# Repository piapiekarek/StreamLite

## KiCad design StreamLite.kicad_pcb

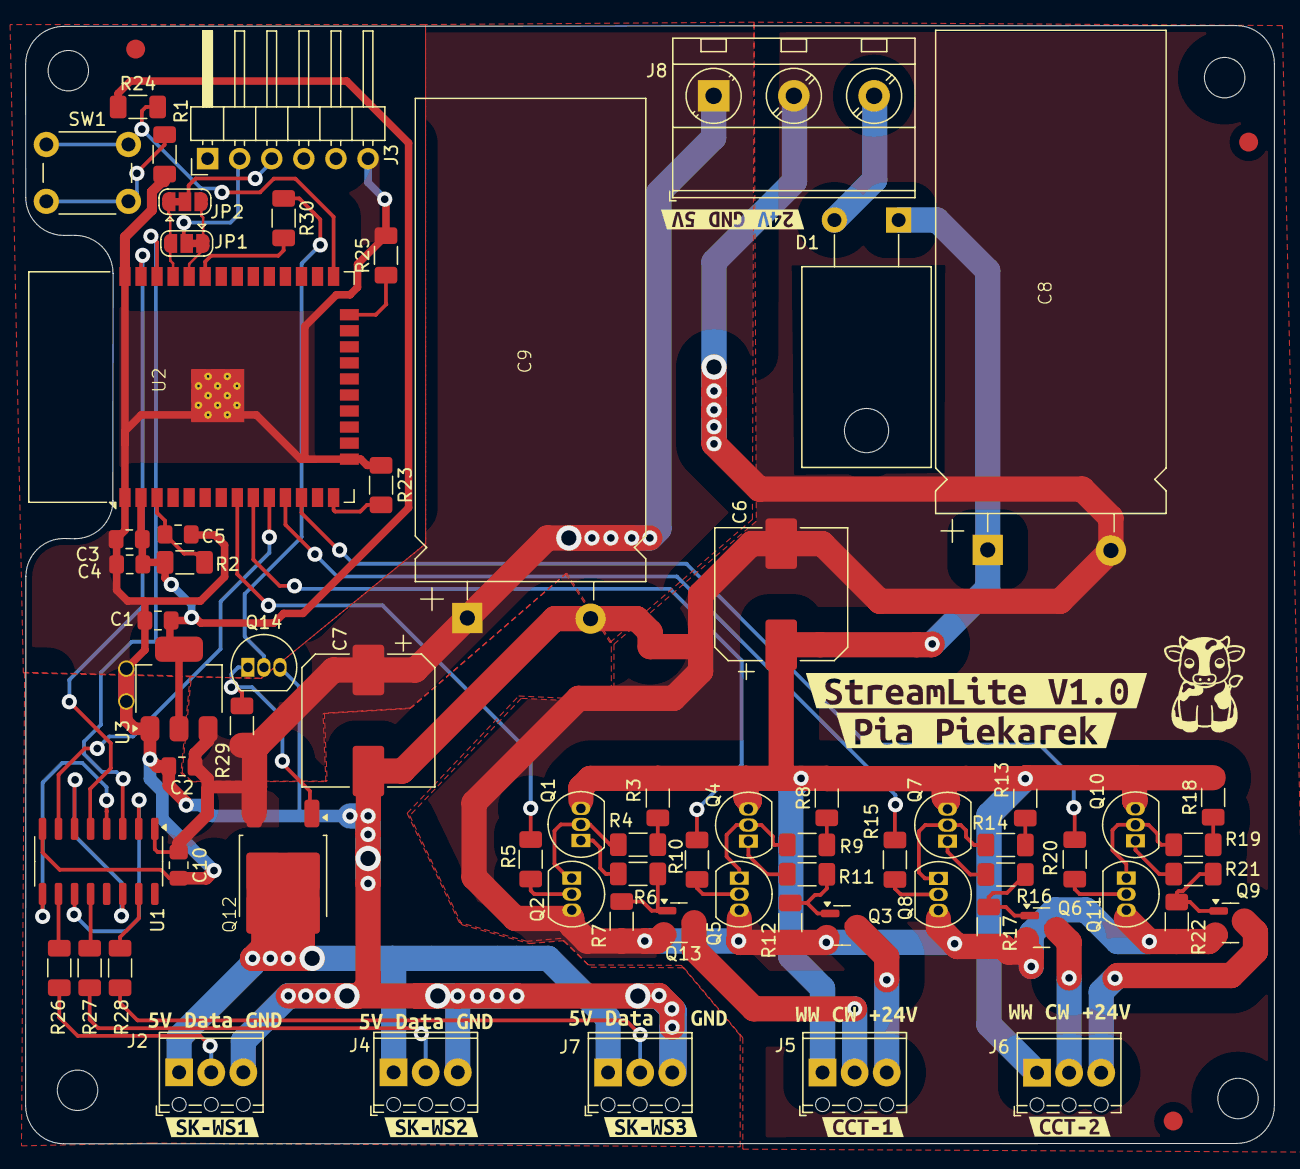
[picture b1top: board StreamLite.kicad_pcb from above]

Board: 2 copper layers, 98.8 x 88.5 mm, 90 parts (1 on the bottom side), 60 nets.

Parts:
C1, C3, C10: 100n; C_0805_2012Metric_Pad1.18x1.45mm_HandSolder
C2: 330n; C_0805_2012Metric_Pad1.18x1.45mm_HandSolder
C4: 10u; C_0805_2012Metric_Pad1.18x1.45mm_HandSolder
C5: 1u; C_0805_2012Metric_Pad1.18x1.45mm_HandSolder
C6, C7: 470u; CP_Elec_10x10
C8, C9: 10.000uF; Capacitor_L38.0mm_D18.0mm_P10_Horizontal
D1: D; TO-220-2_Horizontal_TabDown
FID1, FID2, FID3: Fiducial; Fiducial_1.5mm_Mask3mm
H1, H2, H3, H4: MountingHole; MountingHole_3.2mm_M3
J2, J4, J5, J6, J7: Screw_Terminal_01x03; TerminalBlock_Phoenix_MPT-0,5-3-2.54_1x03_P2.54mm_Horizontal
J3: Conn_01x06_Socket; PinHeader_1x06_P2.54mm_Horizontal
J8: Screw_Terminal_01x03; TerminalBlock_MetzConnect_Type701_RT11L03HGLU_1x03_P6.35mm_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
JP1, JP2: SolderJumper_3_Bridged12; SolderJumper-3_P1.3mm_Bridged12_RoundedPad1.0x1.5mm
NT1: NetTie_2; NetTie-2_SMD_Pad2.0mm
NT2: NetTie_2; NetTie-2_THT_Pad1.0mm
Q1, Q4, Q7, Q10: BC327; TO-92_Inline
Q2, Q5, Q8, Q11: BC337; TO-92_Inline
Q3, Q6, Q9, Q13: AO3400A; SOT-23
Q12: D4185; TO-252-3_TabPin2_D4185
Q14: BC547; TO-92_Inline
R1: 4k7; C_1206_3216Metric_Pad1.33x1.80mm_HandSolder
R2, R3, R5, R8, R10, R13, R15, R18, R20, R24: 10k; C_1206_3216Metric_Pad1.33x1.80mm_HandSolder
R4, R9, R14, R19: 22k; C_1206_3216Metric_Pad1.33x1.80mm_HandSolder
R6, R7, R11, R12, R16, R17, R21, R22, R26, R27, R28, R30: 1k; C_1206_3216Metric_Pad1.33x1.80mm_HandSolder
R23: 10k/DNP; C_1206_3216Metric_Pad1.33x1.80mm_HandSolder
R25: DNP; C_1206_3216Metric_Pad1.33x1.80mm_HandSolder
R29: 2k2; C_1206_3216Metric_Pad1.33x1.80mm_HandSolder
SW1: Boot; SW_PUSH_6mm_H5mm
U1: 4049; SO-16_3.9x9.9mm_P1.27mm
U2: ESP32-WROOM-32; ESP32-Wroom-32
U3: AMS1117-3.3; SOT-223-3_TabPin2
kibuzzard-670D97D1: G***; kibuzzard-670D97D1
kibuzzard-670D99B4, kibuzzard-670D99B4#2: G***; kibuzzard-670D99B4
kibuzzard-670D983B: G***; kibuzzard-670D983B
kibuzzard-670D998F: G***; kibuzzard-670D998F
kibuzzard-670D9849: G***; kibuzzard-670D9849
kibuzzard-670D9857: G***; kibuzzard-670D9857
kibuzzard-670EF237: G***; kibuzzard-670EF237
kibuzzard-670EF243: G***; kibuzzard-670EF243
kibuzzard-67243A6C: G***; kibuzzard-67243A6C
kibuzzard-67243A60: G***; kibuzzard-67243A60
kibuzzard-672436BF: G***; kibuzzard-672436BF
kibuzzard-67243969: G***; kibuzzard-67243969

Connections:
+3V3: C1.1, C3.1, C4.1, R2.1, R24.1, U2.2 (VDD), U3.2 (VO)
+5V: C2.1, C7.1, C9.1, C10.1, J8.1, Q12.3 (S), R29.2, U1.1 (VCC), U3.3 (VI)
+5VP: J2.1, J4.1, J7.1, Q12.1 (D)
+24V: C6.1, C8.1, D1.1 (K), J5.1, J6.1, Q1.3 (E), Q4.3 (E), Q7.3 (E), Q10.3 (E), R3.2, R8.2, R13.2, R18.2
/CW1: J5.2, Q13.3 (D)
/CW2: J6.2, Q6.3 (D)
/V_IN: D1.2 (A), J8.3
/WW1: J5.3, Q3.3 (D)
/WW2: J6.3, Q9.3 (D)
CCT1_CW: R15.1, U2.11 (IO26)
CCT1_WW: R20.1, U2.12 (IO27)
CCT2_CW: R5.1, U2.8 (IO32)
CCT2_WW: R10.1, U2.9 (IO33)
GND1: C6.2, C8.2, J8.2, NT1.1, Q2.3 (E), Q3.2 (S), Q5.3 (E), Q6.2 (S), Q8.3 (E), Q9.2 (S), Q11.3 (E), Q13.2 (S), R7.1, R12.1, R17.1, R22.1
GND2: C2.2, C7.2, C9.2, C10.2, J2.3, J4.3, J7.3, NT1.2, NT2.1, Q14.3 (E), U1.8 (VSS), U3.1 (GND)
GND3: C1.2, C3.2, C4.2, C5.2, J3.6, NT2.2, R1.2, R23.2, R25.2, U2.1 (GND), U2.15 (GND), U2.38 (GND), U2.39 (GND)
LED1: U1.5, U2.37 (IO23)
LED1_H: R26.1, U1.10
LED2: U1.3, U2.36 (IO22)
LED2_H: R27.1, U1.12
LED3: U1.7, U2.10 (IO25)
LED3_H: R28.1, U1.15
unnamed: J2.2, R26.2
unnamed: J3.2, JP1.2 (C)
unnamed: J3.3, JP2.2 (C)
unnamed: J4.2, R27.2
unnamed: J7.2, R28.2
unnamed: Q1.2 (B), Q2.1 (C), R4.1
unnamed: Q1.1 (C), R6.2
unnamed: Q2.2 (B), R5.2
unnamed: Q3.1 (G), R11.1, R12.2
unnamed: Q4.2 (B), Q5.1 (C), R9.1
unnamed: Q4.1 (C), R11.2
unnamed: Q5.2 (B), R10.2
unnamed: Q6.1 (G), R16.1, R17.2
unnamed: Q7.2 (B), Q8.1 (C), R14.1
unnamed: Q7.1 (C), R16.2
unnamed: Q8.2 (B), R15.2
unnamed: Q9.1 (G), R21.1, R22.2
unnamed: Q10.2 (B), Q11.1 (C), R19.1
unnamed: Q10.1 (C), R21.2
unnamed: Q11.2 (B), R20.2
unnamed: Q12.2 (G), Q14.1 (C), R29.1
unnamed: Q13.1 (G), R6.1, R7.2
unnamed: Q14.2 (B), R30.1
unnamed: R1.1, SW1.2
unnamed: R3.1, R4.2
unnamed: R8.1, R9.2
unnamed: R13.1, R14.2
unnamed: R18.1, R19.2
unnamed: U1.4, U1.9
unnamed: U1.2, U1.11
unnamed: U1.6, U1.14
unnamed: C5.1, R2.2, U2.3 (EN)
unnamed: R24.2, SW1.1, U2.25 (IO0)
unnamed: R25.1, U2.24 (IO2)
unnamed: R23.1, U2.14 (IO12)
RX: JP1.3 (B), JP2.1 (A), U2.35 (TXD0/IO1)
Sig_5V_Off: R30.2, U2.33 (IO21)
TX: JP1.1 (A), JP2.3 (B), U2.34 (RXD0/IO3)

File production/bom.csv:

Designator,Footprint,Quantity,Value,LCSC Part #
"C1, C10, C3",0805,3,100n,
C2,0805,1,330n,
C4,0805,1,10u,
C5,0805,1,1u,
"C6, C7",CP_Elec_10x10,2,470u,
"C8, C9",Capacitor_L38.0mm_D18.0mm_P10_Horizontal,2,10.000uF,
D1,TO-220-2_Horizontal_TabDown,1,D,
"J2, J4, J5, J6, J7","TerminalBlock_Phoenix_MPT-0,5-3-2.54_1x03_P2.54mm_Horizontal",5,Screw_Terminal_01x03,
J3,PinHeader_1x06_P2.54mm_Horizontal,1,Conn_01x06_Socket,
J8,TerminalBlock_MetzConnect_Type701_RT11L03HGLU_1x03_P6.35mm_Horizontal,1,Screw_Terminal_01x03,
"Q1, Q10, Q4, Q7",TO-92_Inline,4,BC327,
"Q11, Q2, Q5, Q8",TO-92_Inline,4,BC337,
Q12,TO-252-3_TabPin2_D4185,1,D4185,
"Q13, Q3, Q6, Q9",SOT-23,4,AO3400A,
Q14,TO-92_Inline,1,BC547,
R1,1206,1,4k7,
"R10, R13, R15, R18, R2, R20, R24, R3, R5, R8",1206,10,10k,
"R11, R12, R16, R17, R21, R22, R26, R27, R28, R30, R6, R7",1206,12,1k,
"R14, R19, R4, R9",1206,4,22k,
R23,1206,1,10k/DNP,
R25,1206,1,DNP,
R29,1206,1,2k2,
SW1,SW_PUSH_6mm_H5mm,1,Boot,
U1,SO-16_3.9x9.9mm_P1.27mm,1,4049,
U2,ESP32-Wroom-32,1,ESP32-WROOM-32,
U3,SOT-223-3_TabPin2,1,AMS1117-3.3,

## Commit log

2024-10-15 add parts
2024-10-15 add more parts
2024-10-16 add more tracks
2024-11-19 add schematic
2024-11-23 produced
2024-12-19 changes from weeks ago
2025-01-02 last changes
